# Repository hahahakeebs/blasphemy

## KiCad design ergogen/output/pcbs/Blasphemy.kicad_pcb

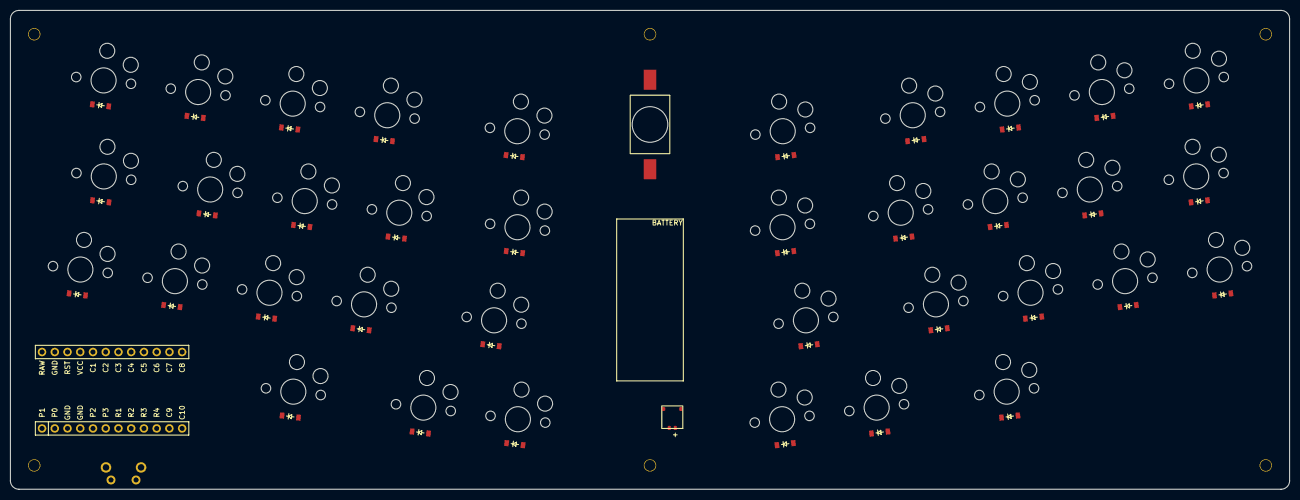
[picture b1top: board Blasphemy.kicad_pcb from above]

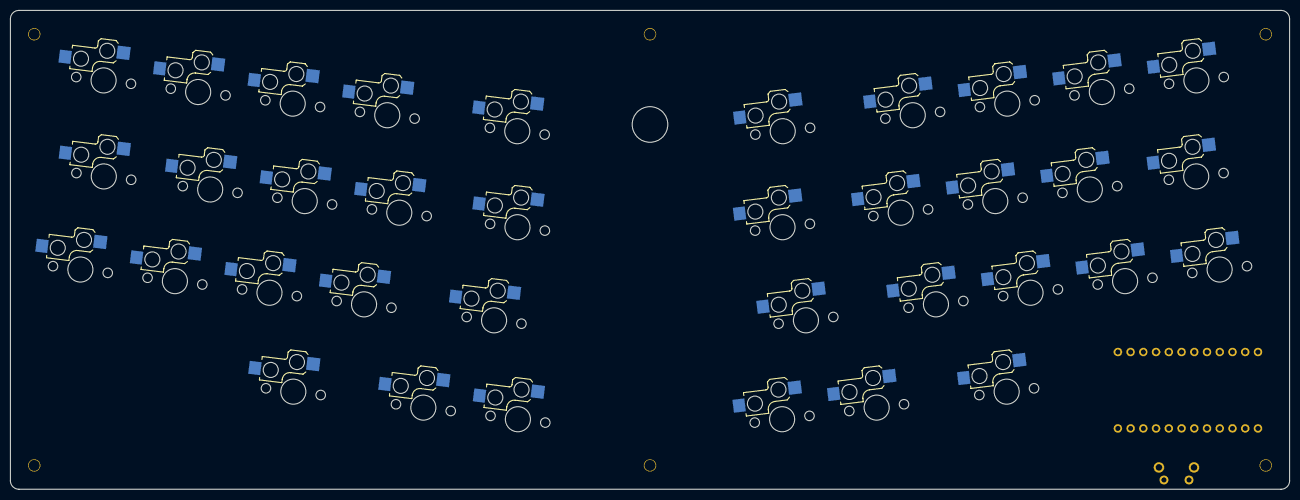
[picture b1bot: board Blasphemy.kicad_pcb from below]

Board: 2 copper layers, 255.1 x 95.5 mm, 82 parts (36 on the bottom side), 54 nets, no tracks yet.

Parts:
CONN1: conn_molex_pico_front
D1, D2, D3, D4, D5, D6, D7, D8, D9, D10, D11, D12, D13, D14, D15, D16, D17, D18, D19, D20, D21, D22, D23, D24, D25, D26, D27, D28, D29, D30, D31, D32, D33, D34, D35, D36: ComboDiode
H1, H2, H3, H4, H5, H6: mounting_hole
MCU1: mcu_nice_nano
S1, S2, S3, S4, S5, S6, S7, S8, S9, S10, S11, S12, S13, S14, S15, S16, S17, S18, S19, S20, S21, S22, S23, S24, S25, S26, S27, S28, S29, S30, S31, S32, S33, S34, S35, S36: switch_choc_v1_v2
S37: SKHLLCA010
SW1: 1208YD

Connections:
BAT_CONN: CONN1.1, SW1.2
C1: MCU1.5, S1.1, S11.1, S21.1
C2: MCU1.6, S2.1, S12.1, S22.1
C3: MCU1.7, S3.1, S13.1, S23.1, S31.1
C4: MCU1.8, S4.1, S14.1, S24.1, S32.1
C5: MCU1.9, S5.1, S15.1, S25.1, S33.1
C6: MCU1.10, S10.1, S20.1, S30.1, S36.1
C7: MCU1.11, S9.1, S19.1, S29.1, S35.1
C8: MCU1.12, S8.1, S18.1, S28.1, S34.1
C9: MCU1.14, S7.1, S17.1, S27.1
C10: MCU1.13, S6.1, S16.1, S26.1
GND: CONN1.2, MCU1.2, MCU1.21, MCU1.22, S37.2
R1: D1.1, D2.1, D3.1, D4.1, D5.1, D6.1, D7.1, D8.1, D9.1, D10.1, MCU1.18
R2: D11.1, D12.1, D13.1, D14.1, D15.1, D16.1, D17.1, D18.1, D19.1, D20.1, MCU1.17
R3: D21.1, D22.1, D23.1, D24.1, D25.1, D26.1, D27.1, D28.1, D29.1, D30.1, MCU1.16
R4: D31.1, D32.1, D33.1, D34.1, D35.1, D36.1, MCU1.15
RAW: MCU1.1, SW1.1
RST: MCU1.3, S37.1
a_home: D11.2, S11.2
b_bottom: D25.2, S25.2
base_thumb: D32.2, S32.2
c_bottom: D23.2, S23.2
d_home: D13.2, S13.2
e_top: D3.2, S3.2
ext_thumb: D33.2, S33.2
f_home: D14.2, S14.2
flex_thumb: D31.2, S31.2
g_home: D15.2, S15.2
mirror_a_home: D16.2, S16.2
mirror_b_bottom: D30.2, S30.2
mirror_base_thumb: D35.2, S35.2
mirror_c_bottom: D28.2, S28.2
mirror_d_home: D18.2, S18.2
mirror_e_top: D8.2, S8.2
mirror_ext_thumb: D36.2, S36.2
mirror_f_home: D19.2, S19.2
mirror_flex_thumb: D34.2, S34.2
mirror_g_home: D20.2, S20.2
mirror_q_top: D6.2, S6.2
mirror_r_top: D9.2, S9.2
mirror_s_home: D17.2, S17.2
mirror_t_top: D10.2, S10.2
mirror_v_bottom: D29.2, S29.2
mirror_w_top: D7.2, S7.2
mirror_x_bottom: D27.2, S27.2
mirror_z_bottom: D26.2, S26.2
q_top: D1.2, S1.2
r_top: D4.2, S4.2
s_home: D12.2, S12.2
t_top: D5.2, S5.2
v_bottom: D24.2, S24.2
w_top: D2.2, S2.2
x_bottom: D22.2, S22.2
z_bottom: D21.2, S21.2

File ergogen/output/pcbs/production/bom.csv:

Designator,Footprint,Quantity,Value,LCSC Part #
CONN1,conn_molex_pico_front,1,,
"D1, D10, D11, D12, D13, D14, D15, D16, D17, D18, D19, D2, D20, D21, D22, D23, D24, D25, D26, D27, D28, D29, D3, D30, D31, D32, D33, D34, D35, D36, D4, D5, D6, D7, D8, D9",diode_mask,36,,
"H1, H2_2, H2, H3, H4, H5_2, H5, H6",mounting_hole,8,,
J1,nice!view,1,nice!view,
"RSW1_2, RSW1",Panasonic_EVQPUL_EVQPUC,2,EVQPUC02K,C79174

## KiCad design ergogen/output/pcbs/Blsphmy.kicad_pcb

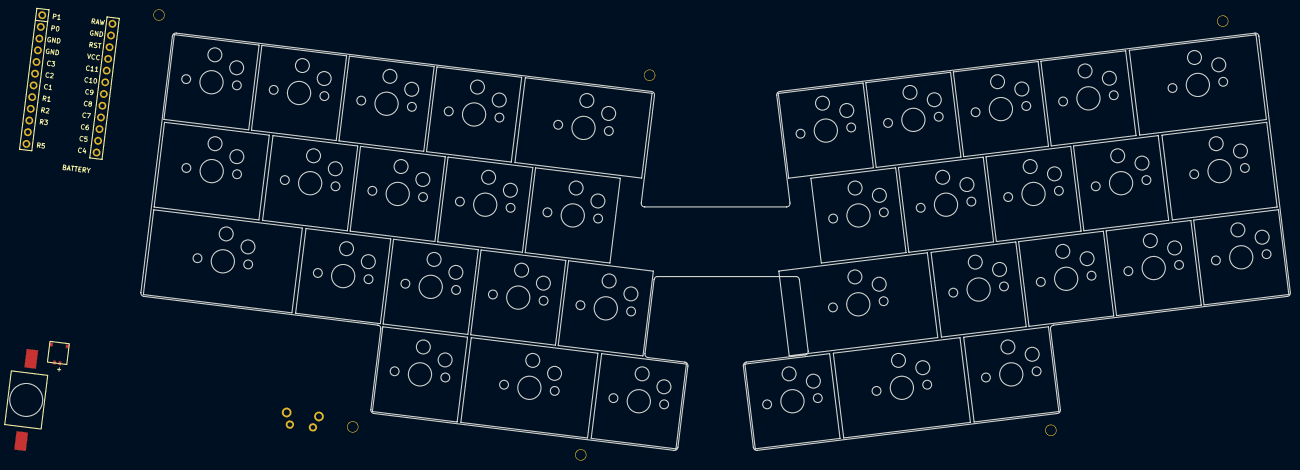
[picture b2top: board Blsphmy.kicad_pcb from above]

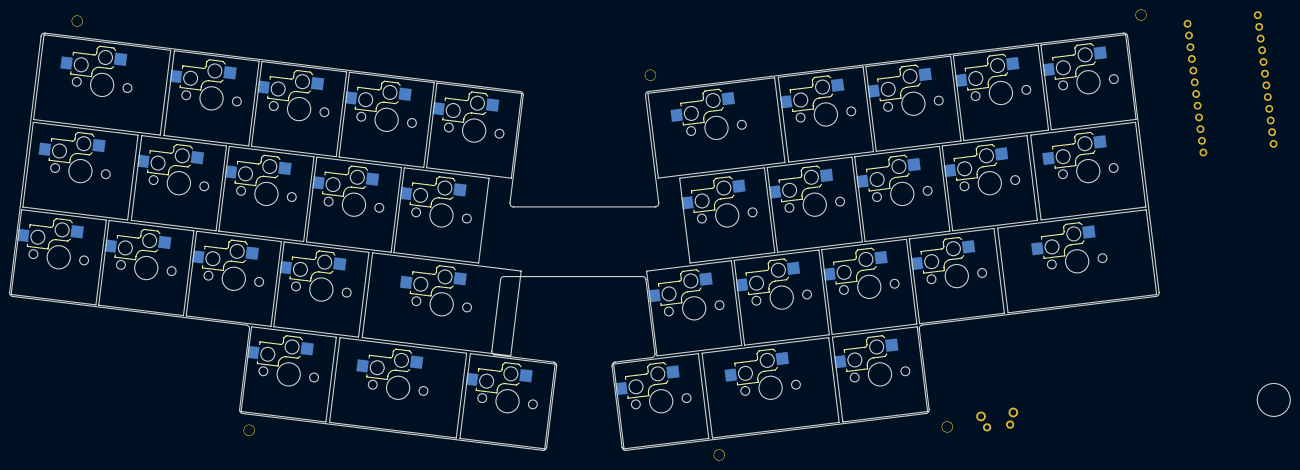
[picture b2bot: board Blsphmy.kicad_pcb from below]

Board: 2 copper layers, 247.7 x 89.9 mm, 46 parts (36 on the bottom side), 14 nets, no tracks yet.

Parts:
CONN1: conn_molex_pico_front
H1, H2, H3, H4, H5, H6: mounting_hole
MCU1: mcu_nice_nano
S1, S2, S3, S4, S5, S6, S7, S8, S9, S10, S11, S12, S13, S14, S15, S16, S17, S18, S19, S20, S21, S22, S23, S24, S25, S26, S27, S28, S29, S30, S31, S32, S33, S34, S35, S36: switch_choc_v1_v2
S37: SKHLLCA010
SW1: 1208YD

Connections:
BAT_CONN: CONN1.1, SW1.2
C1: MCU1.18, S1.1, S11.1, S21.1, S31.1
C2: MCU1.19, S2.1, S12.1, S22.1, S32.1
C3: MCU1.20, S3.1, S13.1, S23.1, S33.1
C4: MCU1.12, S4.1, S14.1, S24.1, S34.1
C5: MCU1.11, S5.1, S15.1, S25.1, S35.1
C6: MCU1.10, S6.1, S16.1, S26.1, S36.1
C7: MCU1.9, S7.1, S17.1, S27.1
C8: MCU1.8, S8.1, S18.1, S28.1
C9: MCU1.7, S9.1, S19.1, S29.1
C10: MCU1.6, S10.1, S20.1, S30.1
GND: CONN1.2, MCU1.2, MCU1.21, MCU1.22, S37.2
RAW: MCU1.1, SW1.1
RST: MCU1.3, S37.1

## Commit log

2025-01-17 init
2025-01-29 add case files
2025-02-14 update config
2025-06-17 added revised blasphemy pcb, cleanup needed
2025-06-18 moved edge cut svg
